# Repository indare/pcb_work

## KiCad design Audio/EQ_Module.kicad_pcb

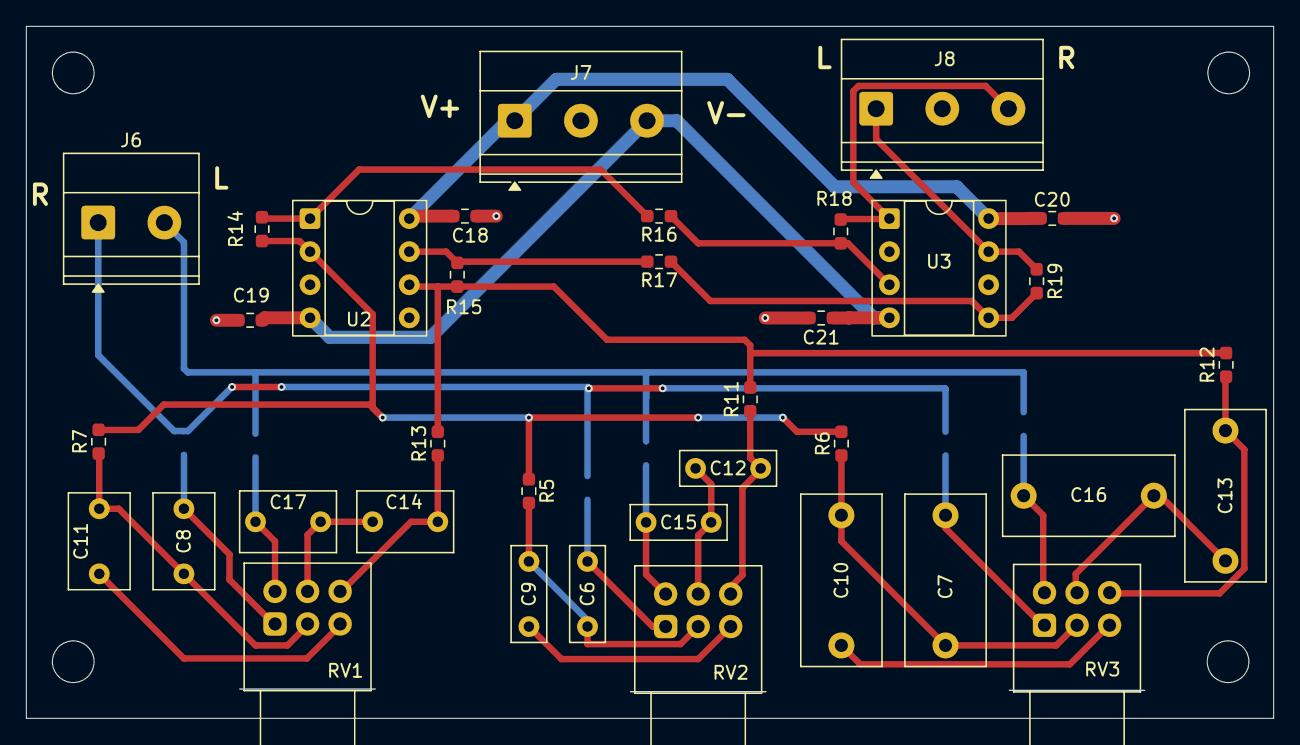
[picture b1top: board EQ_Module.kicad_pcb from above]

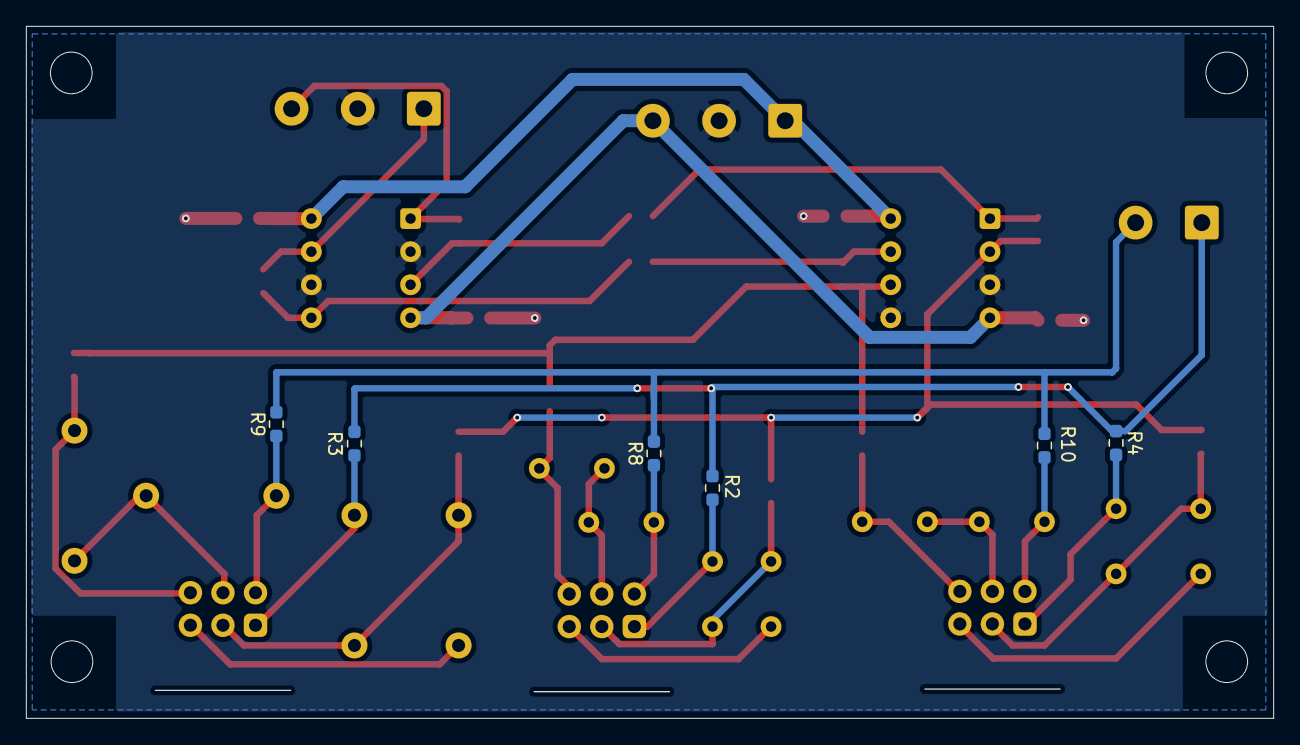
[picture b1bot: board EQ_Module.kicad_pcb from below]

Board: 2 copper layers, 95.8 x 53.2 mm, 46 parts (6 on the bottom side), 31 nets.

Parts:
C6, C9, C12, C15: 0.01uF; C_Rect_L7.2mm_W2.5mm_P5.00mm_FKS2_FKP2_MKS2_MKP2
C7, C10, C13, C16: 2000pF; C_Rect_L13.0mm_W6.0mm_P10.00mm_FKS3_FKP3_MKS4
C8, C11, C14, C17: 0.047μF; C_Rect_L7.2mm_W4.5mm_P5.00mm_FKS2_FKP2_MKS2_MKP2
C18, C19, C20, C21: 0.1μF; R_0603_1608Metric_Pad0.98x0.95mm_HandSolder
H9, H10, H11, H12: MountingHole; MountingHole_3.2mm_M3
J6: AUX_IN; TerminalBlock_Phoenix_MKDS-1,5-2-5.08_1x02_P5.08mm_Horizont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
J7: V_IN; TerminalBlock_Phoenix_MKDS-1,5-3-5.08_1x03_P5.08mm_Horizont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
J8: AUX_OUT; TerminalBlock_Phoenix_MKDS-1,5-3-5.08_1x03_P5.08mm_Horizont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
R2, R3, R4, R5, R6, R7, R8, R9, R10, R11, R12, R13: 10K; R_0603_1608Metric_Pad0.98x0.95mm_HandSolder
R14, R15: 10KΩ; R_0603_1608Metric_Pad0.98x0.95mm_HandSolder
R16, R17, R18, R19: 22KΩ; R_0603_1608Metric_Pad0.98x0.95mm_HandSolder
RV1, RV2, RV3: B100k_Dual; Potentiometer_Alps_RK097_Dual_Horizontal
U2, U3: NJM4558; DIP-8_W7.62mm_Socket

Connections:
/EQModule/L BAX OUT: R11.2, R12.2, R13.2, R15.2, U2.6 (-)
/EQModule/L_IN: J6.2, R8.2, R9.2, R10.2
/EQModule/R BAX OUT: R5.2, R6.2, R7.2, R14.2, U2.2 (-)
/EQModule/R_IN: J6.1, R2.1, R3.1, R4.1
/Rotary_L_IN: J8.1, R19.1, U3.7
/Rotary_R_IN: J8.3, R18.1, U3.1
/Rotary_V+_IN: C18.1, C20.1, J7.1, U2.8 (V+), U3.8 (V+)
/Rotary_V-_IN: C19.2, C21.2, J7.3, U2.4 (V-), U3.4 (V-)
GND: C18.2, C19.1, C20.2, C21.1, J7.2, J8.2, U2.3 (+), U2.5 (+), U3.2 (-), U3.6 (-)
unnamed: C6.1, R2.2, RV2.1
unnamed: C6.2, C9.1, R5.1, RV2.2
unnamed: C7.1, R3.2, RV3.1
unnamed: C8.1, R4.2, RV1.1
unnamed: C9.2, RV2.3
unnamed: C7.2, C10.1, R6.1, RV3.2
unnamed: C10.2, RV3.3
unnamed: C8.2, C11.1, R7.1, RV1.2
unnamed: C11.2, RV1.3
unnamed: C12.1, R11.1, RV2.6
unnamed: C12.2, C15.1, RV2.5
unnamed: C13.1, R12.1, RV3.6
unnamed: C13.2, C16.1, RV3.5
unnamed: C14.1, R13.1, RV1.6
unnamed: C14.2, C17.1, RV1.5
unnamed: C15.2, R8.1, RV2.4
unnamed: C16.2, R9.1, RV3.4
unnamed: C17.2, R10.1, RV1.4
unnamed: R14.1, R16.2, U2.1
unnamed: R15.1, R17.2, U2.7
unnamed: R16.1, R18.2, U3.3 (+)
unnamed: R17.1, R19.2, U3.5 (+)

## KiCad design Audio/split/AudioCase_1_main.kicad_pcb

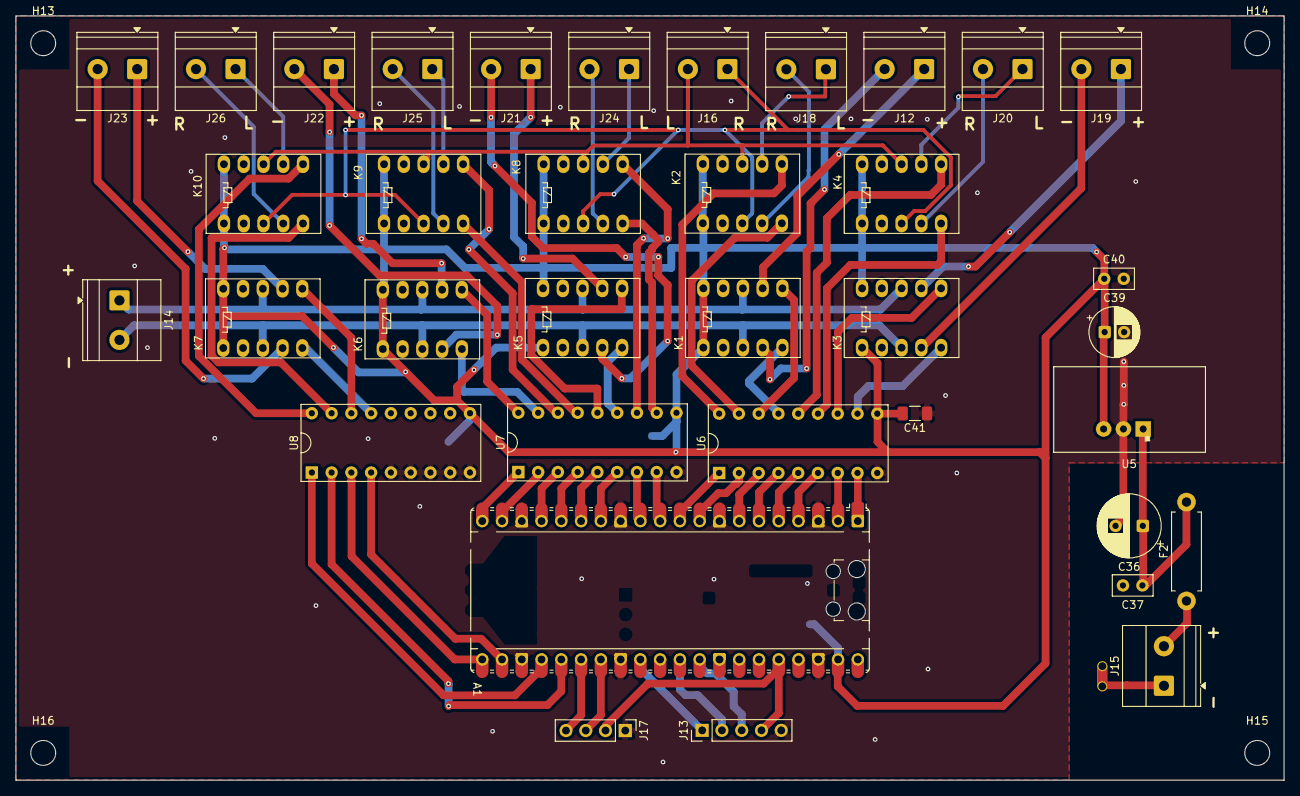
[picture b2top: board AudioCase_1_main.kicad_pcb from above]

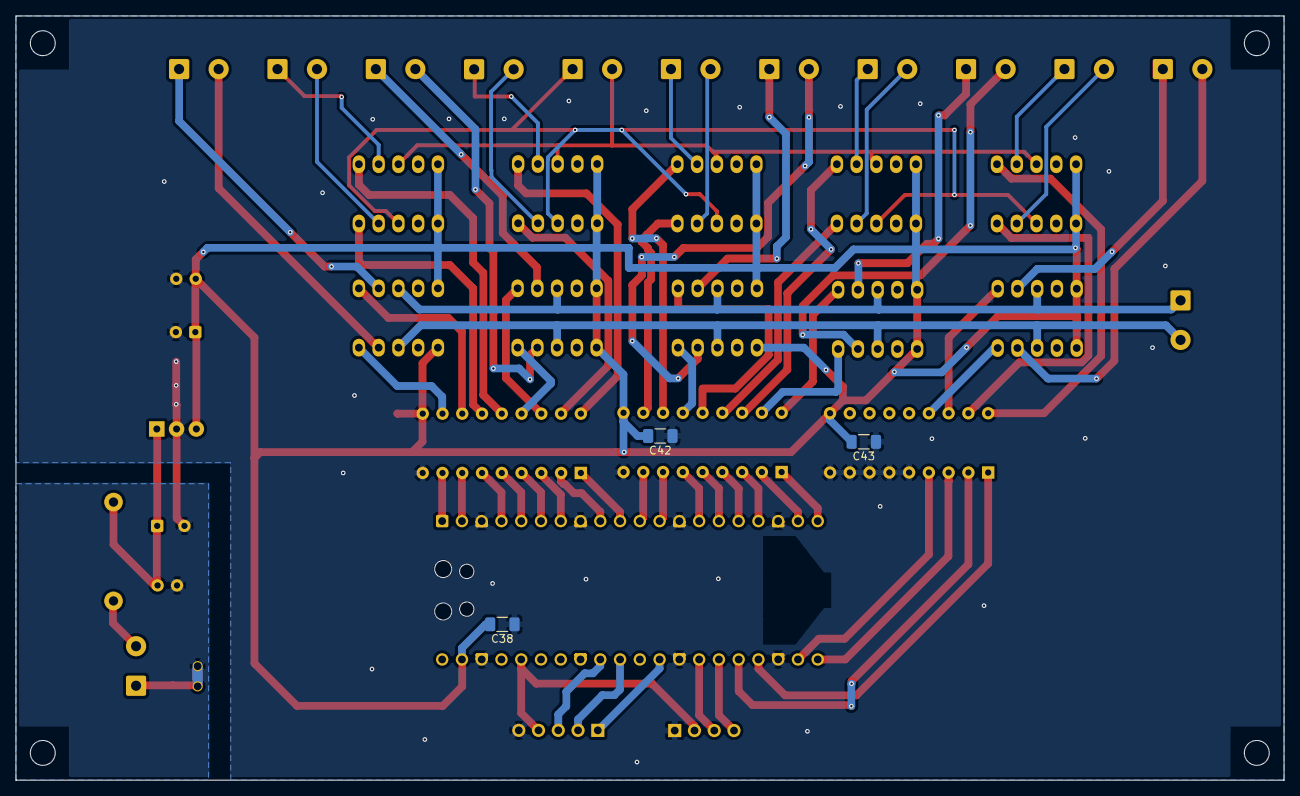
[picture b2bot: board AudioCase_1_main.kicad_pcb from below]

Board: 2 copper layers, 162.9 x 98.2 mm, 44 parts (3 on the bottom side), 75 nets.

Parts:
A1: RaspberryPi_Pico; RaspberryPi_Pico_Common_Unspecified
C36: 47μF; CP_Radial_D8.0mm_P3.50mm
C37, C40: 0.1μF; C_Disc_D5.0mm_W2.5mm_P2.50mm
C38, C41, C42, C43: 0.1μF; C_1206_3216Metric_Pad1.33x1.80mm_HandSolder
C39: 100μF; CP_Radial_D6.3mm_P2.50mm
F2: 1A; R_Axial_DIN0411_L9.9mm_D3.6mm_P12.70mm_Horizontal
H13, H14, H15, H16: MountingHole; MountingHole_3.2mm_M3
J12: AMP1_PWR; TerminalBlock_Phoenix_MKDS-1,5-2-5.08_1x02_P5.08mm_Horizont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
J13: ROTARY_SW; PinHeader_1x05_P2.54mm_Vertical
J14: AMP_PWR_IN; TerminalBlock_Phoenix_MKDS-1,5-2-5.08_1x02_P5.08mm_Horizont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
J15: PD_IN; TerminalBlock_Phoenix_MKDS-1,5-2-5.08_1x02_P5.08mm_Horizont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
J16: AUDIO_IN; TerminalBlock_Phoenix_MKDS-1,5-2-5.08_1x02_P5.08mm_Horizont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
J17: OLED_PIN; PinHeader_1x04_P2.54mm_Vertical
J18: AMP1_LR; TerminalBlock_Phoenix_MKDS-1,5-2-5.08_1x02_P5.08mm_Horizont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
J19: AMP2_PWR; TerminalBlock_Phoenix_MKDS-1,5-2-5.08_1x02_P5.08mm_Horizont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
J20: AMP2_LR; TerminalBlock_Phoenix_MKDS-1,5-2-5.08_1x02_P5.08mm_Horizont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
J21: AMP3_PWR; TerminalBlock_Phoenix_MKDS-1,5-2-5.08_1x02_P5.08mm_Horizont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
J22: AMP4_PWR; TerminalBlock_Phoenix_MKDS-1,5-2-5.08_1x02_P5.08mm_Horizont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
J23: AMP5_PWR; TerminalBlock_Phoenix_MKDS-1,5-2-5.08_1x02_P5.08mm_Horizont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
J24: AMP3_LR; TerminalBlock_Phoenix_MKDS-1,5-2-5.08_1x02_P5.08mm_Horizont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
J25: AMP4_LR; TerminalBlock_Phoenix_MKDS-1,5-2-5.08_1x02_P5.08mm_Horizont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
J26: AMP5_LR; TerminalBlock_Phoenix_MKDS-1,5-2-5.08_1x02_P5.08mm_Horizont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
K1, K2, K3, K4, K5, K6, K7, K8, K9, K10: AZ850P2-x; Relay_DPDT_FRT5
NT1: NetTie_2; NetTie-2_THT_Pad1.0mm
U5: BP5293-50; BP5293-50_ROHM_SIP-3
U6, U7, U8: ULN2803A; ULN2803A_DIP-18_W7.62mm

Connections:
/Controll/3V3: A1.36 (3V3), J13.4, J17.2
/Controll/5V_+: A1.39 (VSYS), C38.2, C39.1, C40.1, C41.2, C42.2, C43.2, K1.1, K1.10, K2.1, K2.10, K3.1, K3.10, K4.1, K4.10, K5.1, K5.10, K6.1, K6.10, K7.1, K7.10, K8.1, K8.10, K9.1, K9.10, K10.1, K10.10, U5.3 (VOUT), U6.10 (COM), U7.10 (COM), U8.10 (COM)
/Controll/+15_IN: F2.1, J15.2
/Controll/AMP_1_L_OUT: J18.1, K2.7
/Controll/AMP_1_R_OUT: J18.2, K2.4
/Controll/AMP_1_V+_OUT: J12.1, K1.7
/Controll/AMP_1_V-_OUT: J12.2, K1.4
/Controll/AMP_2_L_OUT: J20.1, K4.7
/Controll/AMP_2_R_OUT: J20.2, K4.4
/Controll/AMP_2_V+_OUT: J19.1, K3.7
/Controll/AMP_2_V-_OUT: J19.2, K3.4
/Controll/AMP_3_L_OUT: J24.1, K8.7
/Controll/AMP_3_R_OUT: J24.2, K8.4
/Controll/AMP_3_V+_OUT: J21.1, K5.7
/Controll/AMP_3_V-_OUT: J21.2, K5.4
/Controll/AMP_4_L_OUT: J25.1, K9.7
/Controll/AMP_4_R_OUT: J25.2, K9.4
/Controll/AMP_4_V+_OUT: J22.1, K6.7
/Controll/AMP_4_V-_OUT: J22.2, K6.4
/Controll/AMP_5_L_OUT: J26.1, K10.7
/Controll/AMP_5_R_OUT: J26.2, K10.4
/Controll/AMP_5_V+_OUT: J23.1, K7.7
/Controll/AMP_5_V-_OUT: J23.2, K7.4
/Controll/AMP_V+_IN: J14.1, K1.8, K3.8, K5.8, K6.8, K7.8
/Controll/AMP_V-_IN: J14.2, K1.3, K3.3, K5.3, K6.3, K7.3
/Controll/AUDIO_RESET_GPIO_1: A1.2 (GPIO1), U6.7 (I7)
/Controll/AUDIO_RESET_GPIO_2: A1.7 (GPIO5), U6.3 (I3)
/Controll/AUDIO_RESET_GPIO_3: A1.12 (GPIO9), U7.7 (I7)
/Controll/AUDIO_RESET_GPIO_4: A1.17 (GPIO13), U7.3 (I3)
/Controll/AUDIO_RESET_GPIO_5: A1.24 (GPIO18), U8.1 (I1)
/Controll/AUDIO_RESET_RELAY_1: K2.6, U6.18 (O1)
/Controll/AUDIO_RESET_RELAY_2: K4.6, U6.14 (O5)
/Controll/AUDIO_RESET_RELAY_3: K8.6, U7.12 (O7)
/Controll/AUDIO_RESET_RELAY_4: K9.6, U7.16 (O3)
/Controll/AUDIO_RESET_RELAY_5: K10.6, U8.18 (O1)
/Controll/AUDIO_SET_GPIO_1: A1.1 (GPIO0), U6.8 (I8)
/Controll/AUDIO_SET_GPIO_2: A1.6 (GPIO4), U6.4 (I4)
/Controll/AUDIO_SET_GPIO_3: A1.11 (GPIO8), U7.8 (I8)
/Controll/AUDIO_SET_GPIO_4: A1.16 (GPIO12), U7.4 (I4)
/Controll/AUDIO_SET_GPIO_5: A1.25 (GPIO19), U8.2 (I2)
/Controll/AUDIO_SET_RELAY_1: K2.5, U6.17 (O2)
/Controll/AUDIO_SET_RELAY_2: K4.5, U6.13 (O6)
/Controll/AUDIO_SET_RELAY_3: K8.5, U7.11 (O8)
/Controll/AUDIO_SET_RELAY_4: K9.5, U7.15 (O4)
/Controll/AUDIO_SET_RELAY_5: K10.5, U8.17 (O2)
/Controll/CTRL_GND: A1.3 (GND), A1.8 (GND), A1.13 (GND), A1.18 (GND), A1.23 (GND), A1.28 (GND), A1.38 (GND), C36.2, C37.2, C38.1, C39.2, C40.2, C41.1, C42.1, C43.1, J13.5, J17.1, NT1.2, U5.2 (GND), U6.9 (GND), U7.9 (GND), U8.5 (I5), U8.6 (I6), U8.7 (I7), U8.8 (I8), U8.9 (GND)
/Controll/ENC_A: A1.29 (GPIO22), J13.1
/Controll/ENC_B: A1.31 (GPIO26_ADC0), J13.2
/Controll/ENC_SW: A1.32 (GPIO27_ADC1), J13.3
/Controll/L_IN: J16.2, K2.8, K4.8, K8.8, K9.8, K10.8
/Controll/PWR_RESET_GPIO_1: A1.5 (GPIO3), U6.5 (I5)
/Controll/PWR_RESET_GPIO_2: A1.10 (GPIO7), U6.1 (I1)
/Controll/PWR_RESET_GPIO_3: A1.15 (GPIO11), U7.5 (I5)
/Controll/PWR_RESET_GPIO_4: A1.20 (GPIO15), U7.1 (I1)
/Controll/PWR_RESET_GPIO_5: A1.21 (GPIO16), U8.3 (I3)
/Controll/PWR_RESET_RELAY_1: K1.6, U6.16 (O3)
/Controll/PWR_RESET_RELAY_2: K3.6, U6.12 (O7)
/Controll/PWR_RESET_RELAY_3: K5.6, U7.14 (O5)
/Controll/PWR_RESET_RELAY_4: K6.6, U7.18 (O1)
/Controll/PWR_RESET_RELAY_5: K7.6, U8.16 (O3)
/Controll/PWR_SET_GPIO_1: A1.4 (GPIO2), U6.6 (I6)
/Controll/PWR_SET_GPIO_2: A1.9 (GPIO6), U6.2 (I2)
/Controll/PWR_SET_GPIO_3: A1.14 (GPIO10), U7.6 (I6)
/Controll/PWR_SET_GPIO_4: A1.19 (GPIO14), U7.2 (I2)
/Controll/PWR_SET_GPIO_5: A1.22 (GPIO17), U8.4 (I4)
/Controll/PWR_SET_RELAY_1: K1.5, U6.15 (O4)
/Controll/PWR_SET_RELAY_2: K3.5, U6.11 (O8)
/Controll/PWR_SET_RELAY_3: K5.5, U7.13 (O6)
/Controll/PWR_SET_RELAY_4: K6.5, U7.17 (O2)
/Controll/PWR_SET_RELAY_5: K7.5, U8.15 (O4)
/Controll/R_IN: J16.1, K2.3, K4.3, K8.3, K9.3, K10.3
/Controll/SCL: A1.27 (GPIO21), J17.3
/Controll/SDA: A1.26 (GPIO20), J17.4
/MeasurementADC/ADC_GND_IN: J15.1, NT1.1
unnamed: C36.1, C37.1, F2.2, U5.1 (VIN)

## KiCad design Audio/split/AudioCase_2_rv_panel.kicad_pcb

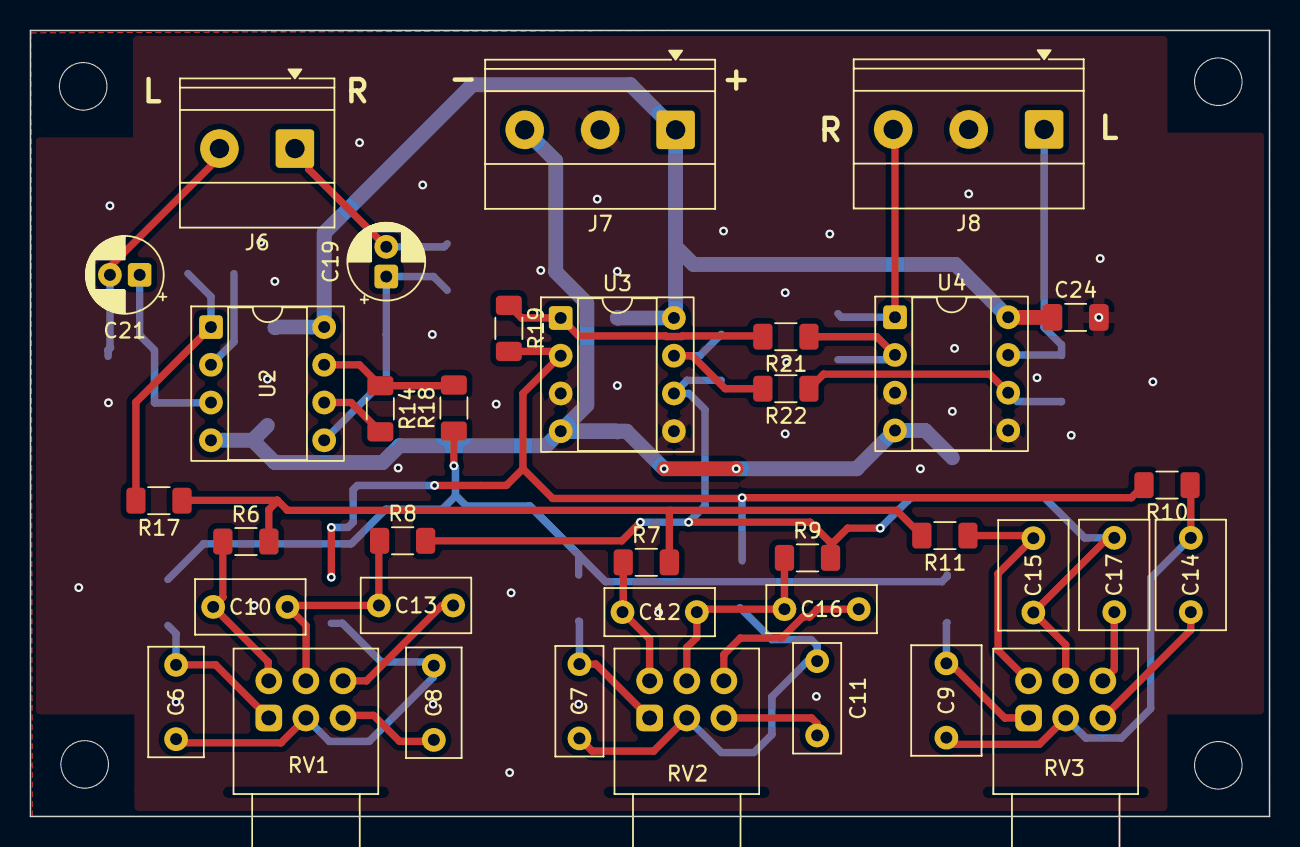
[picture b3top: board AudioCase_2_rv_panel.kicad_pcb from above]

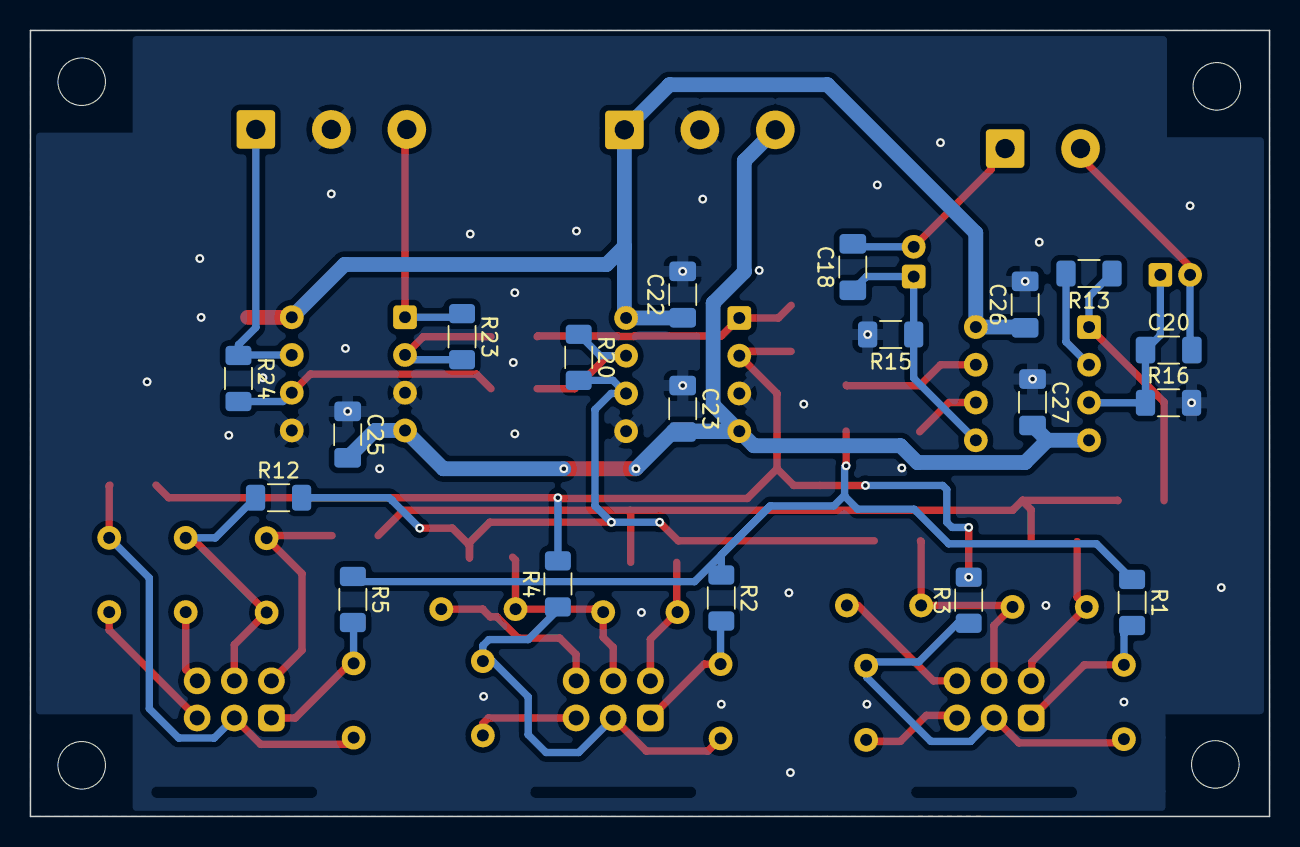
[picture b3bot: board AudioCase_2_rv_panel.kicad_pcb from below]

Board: 2 copper layers, 83.4 x 52.9 mm, 59 parts (19 on the bottom side), 39 nets.

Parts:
C6, C8, C10, C13: 0.047μF; C_Rect_L7.2mm_W3.5mm_P5.00mm_FKS2_FKP2_MKS2_MKP2
C7, C11, C12, C16: 0.01uF; C_Rect_L7.2mm_W3.0mm_P5.00mm_FKS2_FKP2_MKS2_MKP2
C9, C14, C15, C17: 2200pF; C_Rect_L7.2mm_W4.5mm_P5.00mm_FKS2_FKP2_MKS2_MKP2
C18, C20, C22, C23, C24, C25, C26, C27: 0.1μF; C_1206_3216Metric_Pad1.33x1.80mm_HandSolder
C19, C21: 10μF; CP_Radial_D5.0mm_P2.00mm
H5, H6, H7, H8: MountingHole; MountingHole_3.2mm_M3
J6: AUX_IN; TerminalBlock_Phoenix_MKDS-1,5-2-5.08_1x02_P5.08mm_Horizont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
J7: V_IN; TerminalBlock_Phoenix_MKDS-1,5-3-5.08_1x03_P5.08mm_Horizont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
J8: AUX_OUT; TerminalBlock_Phoenix_MKDS-1,5-3-5.08_1x03_P5.08mm_Horizont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
R1, R2, R3, R4, R5, R6, R7, R8, R9, R10, R11, R12: 10K; R_1206_3216Metric_Pad1.30x1.75mm_HandSolder
R13, R14: 0Ω; R_1206_3216Metric_Pad1.30x1.75mm_HandSolder
R15, R16: 47kΩ; R_1206_3216Metric_Pad1.30x1.75mm_HandSolder
R17, R18: 47Ω; R_1206_3216Metric_Pad1.30x1.75mm_HandSolder
R19, R20: 10KΩ; R_1206_3216Metric_Pad1.30x1.75mm_HandSolder
R21, R22, R23, R24: 22KΩ; R_1206_3216Metric_Pad1.30x1.75mm_HandSolder
RV1, RV2, RV3: B100k_Dual; Potentiometer_Alps_RK097_Dual_Horizontal
U2, U3, U4: NJM4558; DIP-8_W7.62mm_Socket

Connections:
/Controll/AMP_V+_IN: C22.1, C24.1, C26.1, J7.1, U2.8 (V+), U3.8 (V+), U4.8 (V+)
/Controll/AMP_V-_IN: C23.2, C25.2, C27.2, J7.3, U2.4 (V-), U3.4 (V-), U4.4 (V-)
/Controll/L_IN: J8.1, R24.1, U4.7
/Controll/R_IN: J8.3, R23.1, U4.1
/EQModule/L_BAX_SUM: R8.2, R9.2, R12.2, R20.2, U3.6 (-)
/EQModule/L_BUFF: R6.2, R7.2, R11.2, R17.1
/EQModule/L_BUFF_IN: C20.1, C21.1, R16.1, U2.3 (+)
/EQModule/L_IN: C20.2, C21.2, J6.2
/EQModule/R_BAX_SUM: R3.2, R4.2, R10.2, R19.2, U3.2 (-)
/EQModule/R_BUFF: R1.1, R2.1, R5.1, R18.1
/EQModule/R_BUFF_IN: C18.1, C19.1, R15.1, U2.5 (+)
/EQModule/R_IN: C18.2, C19.2, J6.1
GND: C22.2, C23.1, C24.2, C25.1, C26.2, C27.1, J7.2, J8.2, R15.2, R16.2, U3.3 (+), U3.5 (+), U4.3 (+), U4.5 (+)
unnamed: C6.1, R1.2, RV1.1
unnamed: C6.2, C8.1, R3.1, RV1.2
unnamed: C7.1, R2.2, RV2.1
unnamed: C8.2, RV1.3
unnamed: C9.1, R5.2, RV3.1
unnamed: C10.1, C13.2, R8.1, RV1.5
unnamed: C10.2, R6.1, RV1.4
unnamed: C7.2, C11.1, R4.1, RV2.2
unnamed: C11.2, RV2.3
unnamed: C12.1, C16.1, R9.1, RV2.5
unnamed: C12.2, R7.1, RV2.4
unnamed: C13.1, RV1.6
unnamed: C9.2, C14.1, R10.1, RV3.2
unnamed: C14.2, RV3.3
unnamed: C15.1, C17.1, R12.1, RV3.5
unnamed: C15.2, R11.1, RV3.4
unnamed: C16.2, RV2.6
unnamed: C17.2, RV3.6
unnamed: R13.1, R17.2, U2.1
unnamed: R14.1, R18.2, U2.7
unnamed: R19.1, R21.2, U3.1
unnamed: R20.1, R22.2, U3.7
unnamed: R13.2, U2.2 (-)
unnamed: R14.2, U2.6 (-)
unnamed: R21.1, R23.2, U4.2 (-)
unnamed: R22.1, R24.2, U4.6 (-)

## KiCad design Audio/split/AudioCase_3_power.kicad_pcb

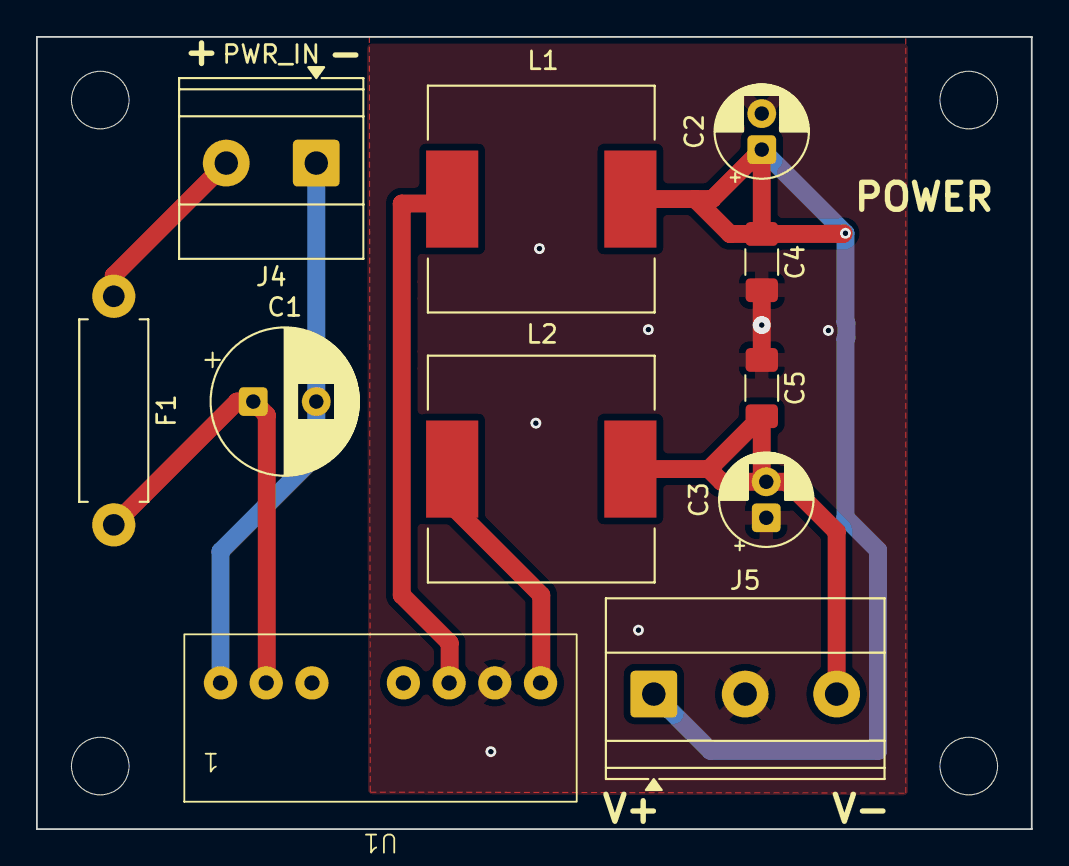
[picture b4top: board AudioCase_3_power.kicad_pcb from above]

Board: 2 copper layers, 55.3 x 44.0 mm, 15 parts (0 on the bottom side), 8 nets.

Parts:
C1: 47μF; CP_Radial_D8.0mm_P3.50mm
C2, C3: 4.7μF; CP_Radial_D5.0mm_P2.00mm
C4, C5: 0.1μF; C_1206_3216Metric_Pad1.33x1.80mm_HandSolder
F1: 1A; R_Axial_DIN0411_L9.9mm_D3.6mm_P12.70mm_Horizontal
H1, H2, H3, H4: MountingHole; MountingHole_3.2mm_M3
J4: PWR_IN; TerminalBlock_Phoenix_MKDS-1,5-2_1x02_P5.00mm_Horizontal
J5: PWR_OUT; TerminalBlock_Phoenix_MKDS-1,5-3-5.08_1x03_P5.08mm_Horizont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
L1, L2: L; L_12x12mm_H8mm
U1: MCW03; MCW03-12D15_SIP7_THT

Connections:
/Controll/+15_IN: F1.1, J4.2
/Controll/AMP_V+_IN: C2.1, C4.1, J5.1, L1.1
/Controll/AMP_V-_IN: C3.2, C5.2, J5.3, L2.2
/MeasurementADC/ADC_GND_IN: C1.2, J4.1, U1.1 (GND)
GND: C2.2, C3.1, C4.2, C5.1, J5.2, U1.7 (Common)
unnamed: C1.1, F1.2, U1.2 (+Vin)
unnamed: L1.2, U1.6 (+Vout)
unnamed: L2.1, U1.8 (-Vout)

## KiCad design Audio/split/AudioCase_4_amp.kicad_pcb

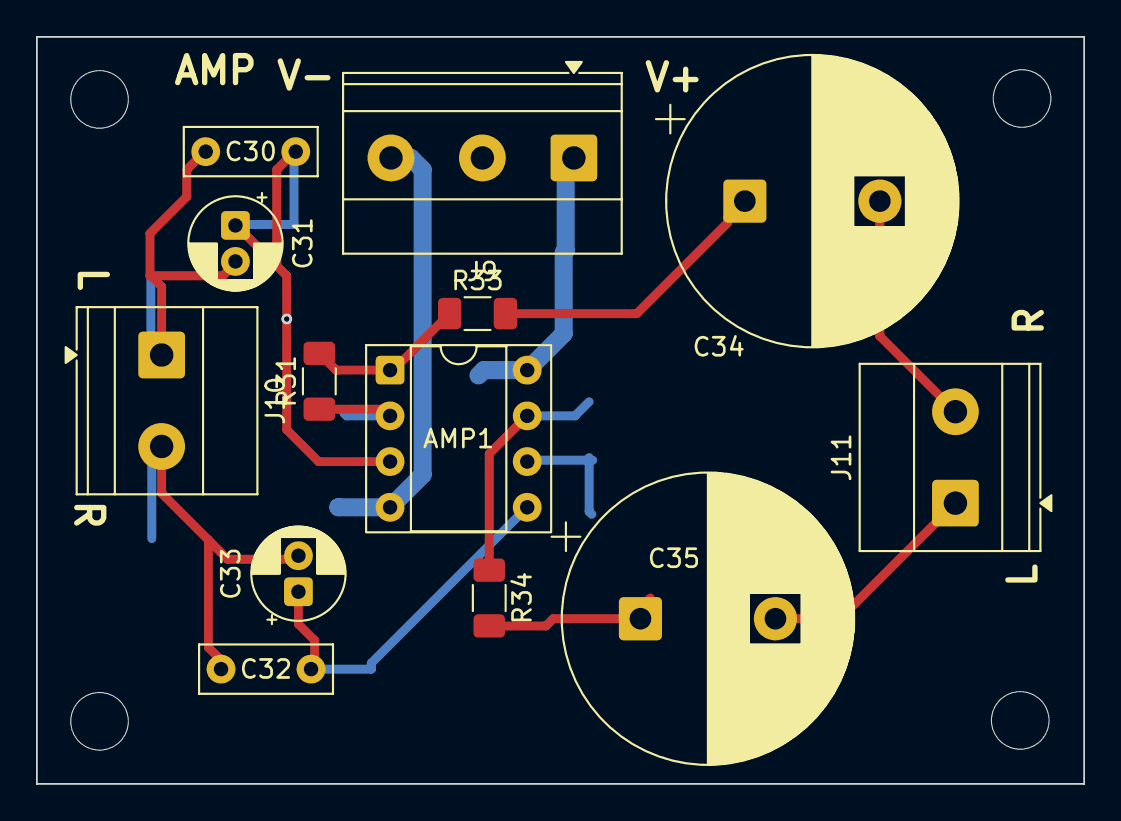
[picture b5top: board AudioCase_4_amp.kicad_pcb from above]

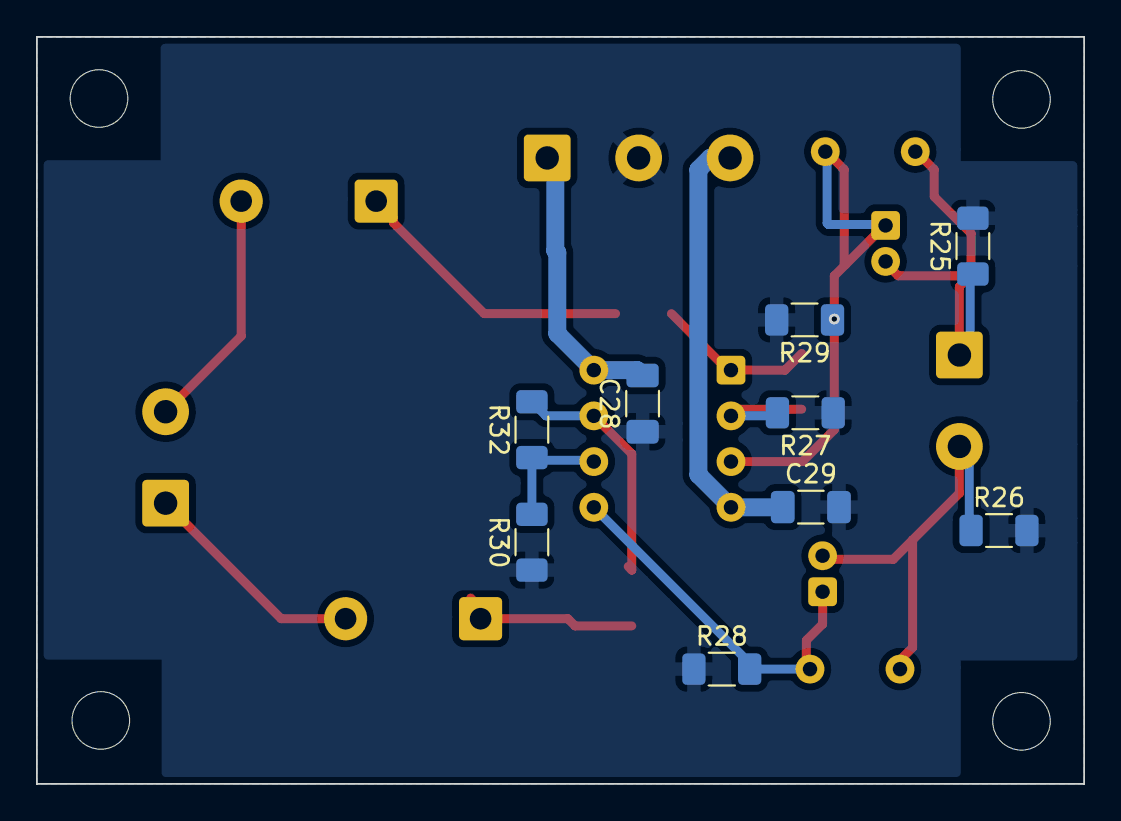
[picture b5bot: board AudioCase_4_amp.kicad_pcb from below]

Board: 2 copper layers, 58.2 x 41.5 mm, 26 parts (9 on the bottom side), 15 nets.

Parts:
AMP1: NE5532; DIP-8_W7.62mm_Socket
C28, C29: 0.1μF; C_1206_3216Metric_Pad1.33x1.80mm_HandSolder
C30, C32: 0.1μF; C_Rect_L7.2mm_W2.5mm_P5.00mm_FKS2_FKP2_MKS2_MKP2
C31, C33: 10μF; CP_Radial_D5.0mm_P2.00mm
C34, C35: 470μF; CP_Radial_D16.0mm_P7.50mm
H9, H10, H11, H12: MountingHole; MountingHole_3.2mm_M3
J9: AMP_PWR; TerminalBlock_Phoenix_MKDS-1,5-3-5.08_1x03_P5.08mm_Horizont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
J10: AMP_AUX_IN; TerminalBlock_Phoenix_MKDS-1,5-2-5.08_1x02_P5.08mm_Horizont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
J11: AMP_AUX_OUT; TerminalBlock_Phoenix_MKDS-1,5-2-5.08_1x02_P5.08mm_Horizont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
R25, R26: 220KΩ; R_1206_3216Metric_Pad1.30x1.75mm_HandSolder
R27, R28, R29, R30: 10KΩ; R_1206_3216Metric_Pad1.30x1.75mm_HandSolder
R31, R32: 47KΩ; R_1206_3216Metric_Pad1.30x1.75mm_HandSolder
R33, R34: 47Ω; R_1206_3216Metric_Pad1.30x1.75mm_HandSolder

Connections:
/AmpModule/L_IN: C32.2, C33.2, J10.2, R26.1
/AmpModule/R_IN: C30.2, C31.2, J10.1, R25.1
/AmpModule/V+_IN: AMP1.8 (V+), C28.2, J9.1
/AmpModule/V-_IN: AMP1.4 (V-), C29.1, J9.3
/MeasurementADC/AUDIO_L_IN: C35.2, J11.1
/MeasurementADC/AUDIO_R_IN: C34.2, J11.2
GND: C28.1, C29.2, J9.2, R25.2, R26.2, R27.1, R28.1, R29.2, R30.1
unnamed: AMP1.1, R31.2, R33.1
unnamed: AMP1.7, R32.2, R34.1
unnamed: AMP1.3 (+), C30.1, C31.1, R29.1
unnamed: AMP1.2 (-), R27.2, R31.1
unnamed: AMP1.5 (+), C32.1, C33.1, R28.2
unnamed: AMP1.6 (-), R30.2, R32.1
unnamed: C34.1, R33.2
unnamed: C35.1, R34.2

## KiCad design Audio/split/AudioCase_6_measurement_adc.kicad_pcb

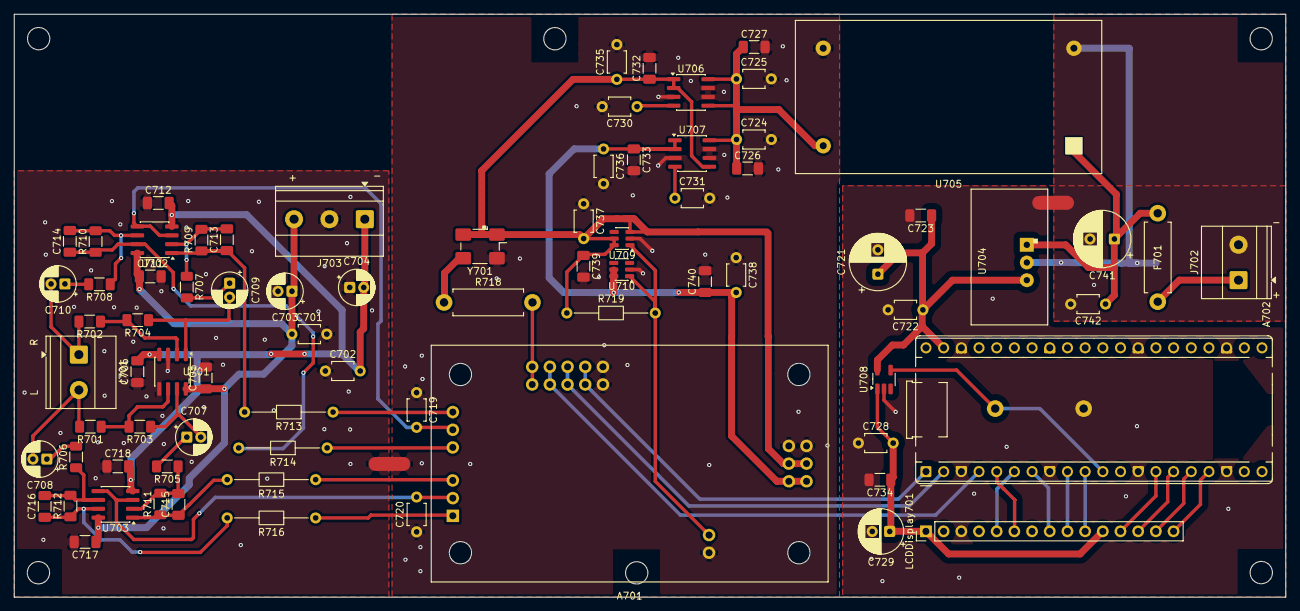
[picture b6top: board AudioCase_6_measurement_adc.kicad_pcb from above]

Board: 2 copper layers, 182.6 x 83.7 mm, 87 parts (1 on the bottom side), 56 nets.

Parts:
A701: ADC1804_F_MODULE; ADC1804_F_KYOHRITSU_56x33mm
A702: Pico2; RaspberryPi_Pico_Common_THT
C701, C702, C719, C720, C722, C724, C725, C728, C735, C736, C742: 100nF; C_Murata_RDE_L4.0mm_W3.5mm_T2.5mm_P5.00mm
C703, C704: 10uF 50V; CP_Radial_D5.0mm_P2.00mm
C705, C706, C711, C712, C717, C718: 100nF; C_1206_3216Metric_Pad1.33x1.80mm_HandSolder
C707, C708, C709, C710: 10uF 25V; CP_Radial_D5.0mm_P2.00mm
C713, C714, C715, C716: 1.8nF C0G; C_1206_3216Metric_Pad1.33x1.80mm_HandSolder
C721: 47uF; CP_Radial_D8.0mm_P3.50mm
C723, C734: 10uF; C_1206_3216Metric_Pad1.33x1.80mm_HandSolder
C726, C727, C733: 10uF 16V X7R; C_1206_3216Metric_Pad1.33x1.80mm_HandSolder
C729: 22uF; CP_Radial_D6.3mm_P2.50mm
C730, C731, C737, C738: 10nF; C_Murata_RDE_L4.0mm_W3.5mm_T2.5mm_P5.00mm
C732: 10uF 10V X7R; C_1206_3216Metric_Pad1.33x1.80mm_HandSolder
C739, C740: 10uF 50V X7R; C_1206_3216Metric_Pad1.33x1.80mm_HandSolder
C741: 47uF 35V; CP_Radial_D8.0mm_P3.50mm
F701: Fuse; R_Axial_DIN0411_L9.9mm_D3.6mm_P12.70mm_Horizontal
H11, H11#2, H11#3, H11#4, H11#5, H11#6: MountingHole; MountingHole_3.2mm_M3
J701: AUDIO; TerminalBlock_Phoenix_MKDS-1,5-2-5.08_1x02_P5.08mm_Horizont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
J702: V_IN; TerminalBlock_Phoenix_MKDS-1,5-2-5.08_1x02_P5.08mm_Horizont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
J703: 15_V_IN; TerminalBlock_Phoenix_MKDS-1,5-3-5.08_1x03_P5.08mm_Horizont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
LCDDisplay701: WAVESHARE-29318; PinHeader_1x15_P2.54mm_Vertical
NT701: A_GND-ADC_GND; NetTie-2_SMD_Pad2.0mm
NT702: ADC_GND_IN-D_GND; NetTie-2_SMD_Pad2.0mm
R701, R702, R703, R704: 4.7k 0.1%; R_1206_3216Metric_Pad1.30x1.75mm_HandSolder
R705, R706, R707, R708: 3.3k 0.1%; R_1206_3216Metric_Pad1.30x1.75mm_HandSolder
R709, R710, R711, R712: 1k 0.1%; R_1206_3216Metric_Pad1.30x1.75mm_HandSolder
R713, R714, R715, R716: 47 Takman 1/4W; R_Axial_Takman_RLC25S_L3.3mm_D1.7mm_P12.70mm_Horizontal
R717: 100k; R_Axial_DIN0411_L9.9mm_D3.6mm_P12.70mm_Horizontal
R718: 33 MCLK; R_Axial_DIN0411_L9.9mm_D3.6mm_P12.70mm_Horizontal
R719: 10k Takman 1/4W OD; R_Axial_Takman_RLC25S_L3.3mm_D1.7mm_P12.70mm_Horizontal
U701, U702, U703: OPA1656; SOIC-8_3.9x4.9mm_P1.27mm
U704: BP5293-50; BP5293-50_ROHM_SIP-3
U705: MBC2596-01; MBC2596-01_TAEJIN_43x21mm
U706: LT1763-3.3; SOIC-8_3.9x4.9mm_P1.27mm
U707: LT1763-5; SOIC-8_3.9x4.9mm_P1.27mm
U708: XC8107AC20MR-G; SOT-23-5_HandSoldering
U709: TPS3808G33DBVR; SOT-23-6
U710: TPS3808G50DBVR; SOT-23-6
Y701: ASFL1-12.288MHZ-EC-T; Oscillator_SMD_Abracon_ASFL-4Pin_5.0x3.2mm_HandSoldering

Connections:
/Controll/+15_IN: C741.1, C742.1, F701.2, U704.1 (VIN), U705.1 (IN+)
/Controll/AMP_V+_IN: C701.1, C703.1, C705.1, C711.1, C717.1, J703.3, U701.8 (V+), U702.8 (V+), U703.8 (V+)
/Controll/AMP_V-_IN: C702.2, C704.2, C706.2, C712.2, C718.2, J703.1, U701.4 (V-), U702.4 (V-), U703.4 (V-)
/MeasurementADC/+3V3_A: A701.13 (+3V3), C732.1, C735.1, C737.2, C739.1, R719.1, U706.1 (OUT), U706.2 (SENSE), U707.5 (SHDN), U709.3 (~MR), U709.5 (SENSE), U709.6 (VDD), Y701.1 (ST), Y701.4 (VDD)
/MeasurementADC/+5V_A: A701.12 (+5V), C733.1, C736.1, C738.2, C740.1, U707.1 (OUT), U707.2 (SENSE), U710.5 (SENSE), U710.6 (VDD)
/MeasurementADC/+5V_D: A702.39 (VSYS), C721.1, C722.1, C723.1, U704.3 (VOUT), U708.5 (VIN)
/MeasurementADC/ADC_BCK: A701.9 (BCK), A702.2 (GPIO1)
/MeasurementADC/ADC_DATA: A701.10 (DATA), A702.1 (GPIO0)
/MeasurementADC/ADC_GND: A701.14 (GND), C719.1, C720.1, C724.2, C725.2, C726.2, C727.2, C730.2, C731.2, C732.2, C733.2, C735.2, C736.2, C737.1, C738.1, C739.2, C740.2, NT701.1, U705.4 (OUT-), U706.3 (GND), U706.6 (GND), U706.7 (GND), U707.3 (GND), U707.6 (GND), U707.7 (GND), U709.2 (GND), U710.2 (GND), Y701.2 (GND)
/MeasurementADC/ADC_GND_IN: C741.2, C742.2, J702.2, NT702.1, U704.2 (GND), U705.2 (IN-)
/MeasurementADC/ADC_LRCK: A701.8 (LRCK), A702.4 (GPIO2)
/MeasurementADC/ADC_MCLK: A701.7 (SCKI), R718.2
/MeasurementADC/ADC_nRST: A701.11 (RST), R719.2, U709.1 (~RESET), U710.1 (~RESET)
/MeasurementADC/AUDIO_L_IN: C708.2, J701.2, R701.2
/MeasurementADC/AUDIO_R_IN: C710.2, J701.1, R702.2
/MeasurementADC/D_GND: A702.3 (GND), A702.8 (GND), A702.13 (GND), A702.18 (GND), A702.23 (GND), A702.28 (GND), A702.38 (GND), C721.2, C722.2, C723.2, C728.1, C729.2, C734.2, LCDDisplay701.3 (GND), NT702.2, R717.2, U708.2 (VSS)
/MeasurementADC/LCD_CS: A702.7 (GPIO5), LCDDisplay701.8 (LCD_CS)
/MeasurementADC/LCD_DC: A702.9 (GPIO6), LCDDisplay701.9 (LCD_DC)
/MeasurementADC/LCD_EN: A702.11 (GPIO8), R717.1, U708.4 (CE)
/MeasurementADC/LCD_MOSI: A702.6 (GPIO4), LCDDisplay701.5 (MOSI)
/MeasurementADC/LCD_RST: A702.10 (GPIO7), LCDDisplay701.10 (LCD_RST)
/MeasurementADC/LCD_SCK: A702.5 (GPIO3), LCDDisplay701.6 (SCLK)
/MeasurementADC/LCD_VCC: C728.2, C729.1, C734.1, LCDDisplay701.1 (VCC), LCDDisplay701.11 (LCD_BL), U708.1 (VOUT)
/MeasurementADC/PICO_3V3: A702.30 (RUN), A702.35 (ADC_VREF), A702.36 (3V3), A702.37 (3V3_EN)
/MeasurementADC/TP_INT: A702.16 (GPIO12), LCDDisplay701.14 (TP_INT)
/MeasurementADC/TP_RST: A702.17 (GPIO13), LCDDisplay701.15 (TP_RST)
/MeasurementADC/TP_SCL: A702.15 (GPIO11), LCDDisplay701.13 (TP_SCL)
/MeasurementADC/TP_SDA: A702.14 (GPIO10), LCDDisplay701.12 (TP_SDA)
/MeasurementADC/VCOML: A701.2 (VCOML), C720.2, U703.3 (INA+), U703.5 (INB+)
/MeasurementADC/VCOMR: A701.5 (VCOMR), C719.2, U702.3 (INA+), U702.5 (INB+)
/MeasurementADC/VINL+: A701.1 (VINL+), R716.1
/MeasurementADC/VINL-: A701.3 (VINL-), R715.1
/MeasurementADC/VINR+: A701.6 (VINR+), R714.1
/MeasurementADC/VINR-: A701.4 (VINR-), R713.1
GND: C701.2, C702.1, C703.2, C704.1, C705.2, C706.1, C711.2, C712.1, C717.2, C718.1, J703.2, NT701.2, U701.3 (INA+), U701.5 (INB+)
unnamed: C707.1, R705.2
unnamed: C708.1, R706.2
unnamed: C709.1, R707.2
unnamed: C710.1, R708.2
unnamed: F701.1, J702.1
unnamed: R702.1, R704.2, U701.2 (INA-)
unnamed: C709.2, R704.1, U701.1 (OUTA)
unnamed: R701.1, R703.2, U701.6 (INB-)
unnamed: C707.2, R703.1, U701.7 (OUTB)
unnamed: C713.2, R707.1, R709.2, U702.2 (INA-)
unnamed: C713.1, R709.1, R713.2, U702.1 (OUTA)
unnamed: C714.2, R708.1, R710.2, U702.6 (INB-)
unnamed: C714.1, R710.1, R714.2, U702.7 (OUTB)
unnamed: C715.2, R705.1, R711.2, U703.2 (INA-)
unnamed: C715.1, R711.1, R715.2, U703.1 (OUTA)
unnamed: C716.2, R706.1, R712.2, U703.6 (INB-)
unnamed: C716.1, R712.1, R716.2, U703.7 (OUTB)
unnamed: C724.1, C725.1, C726.1, C727.1, U705.3 (OUT+), U706.5 (SHDN), U706.8 (IN), U707.8 (IN)
unnamed: C730.1, U706.4 (BYP)
unnamed: C731.1, U707.4 (BYP)
unnamed: R718.1, Y701.3 (OUT)
